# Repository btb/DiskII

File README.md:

# DiskII
 An Apple Disk II controller clone using standard EPROMs

Revision 0 of this board is broken, [here's how to fix it](https://github.com/btb/DiskII/wiki/Revision-0-errata).

[Revision 1](https://github.com/btb/DiskII/releases/tag/rev1) has all known problems fixed.

[Interactive BOM](https://btb.github.io/DiskII/bom/DiskII_rev1.html)

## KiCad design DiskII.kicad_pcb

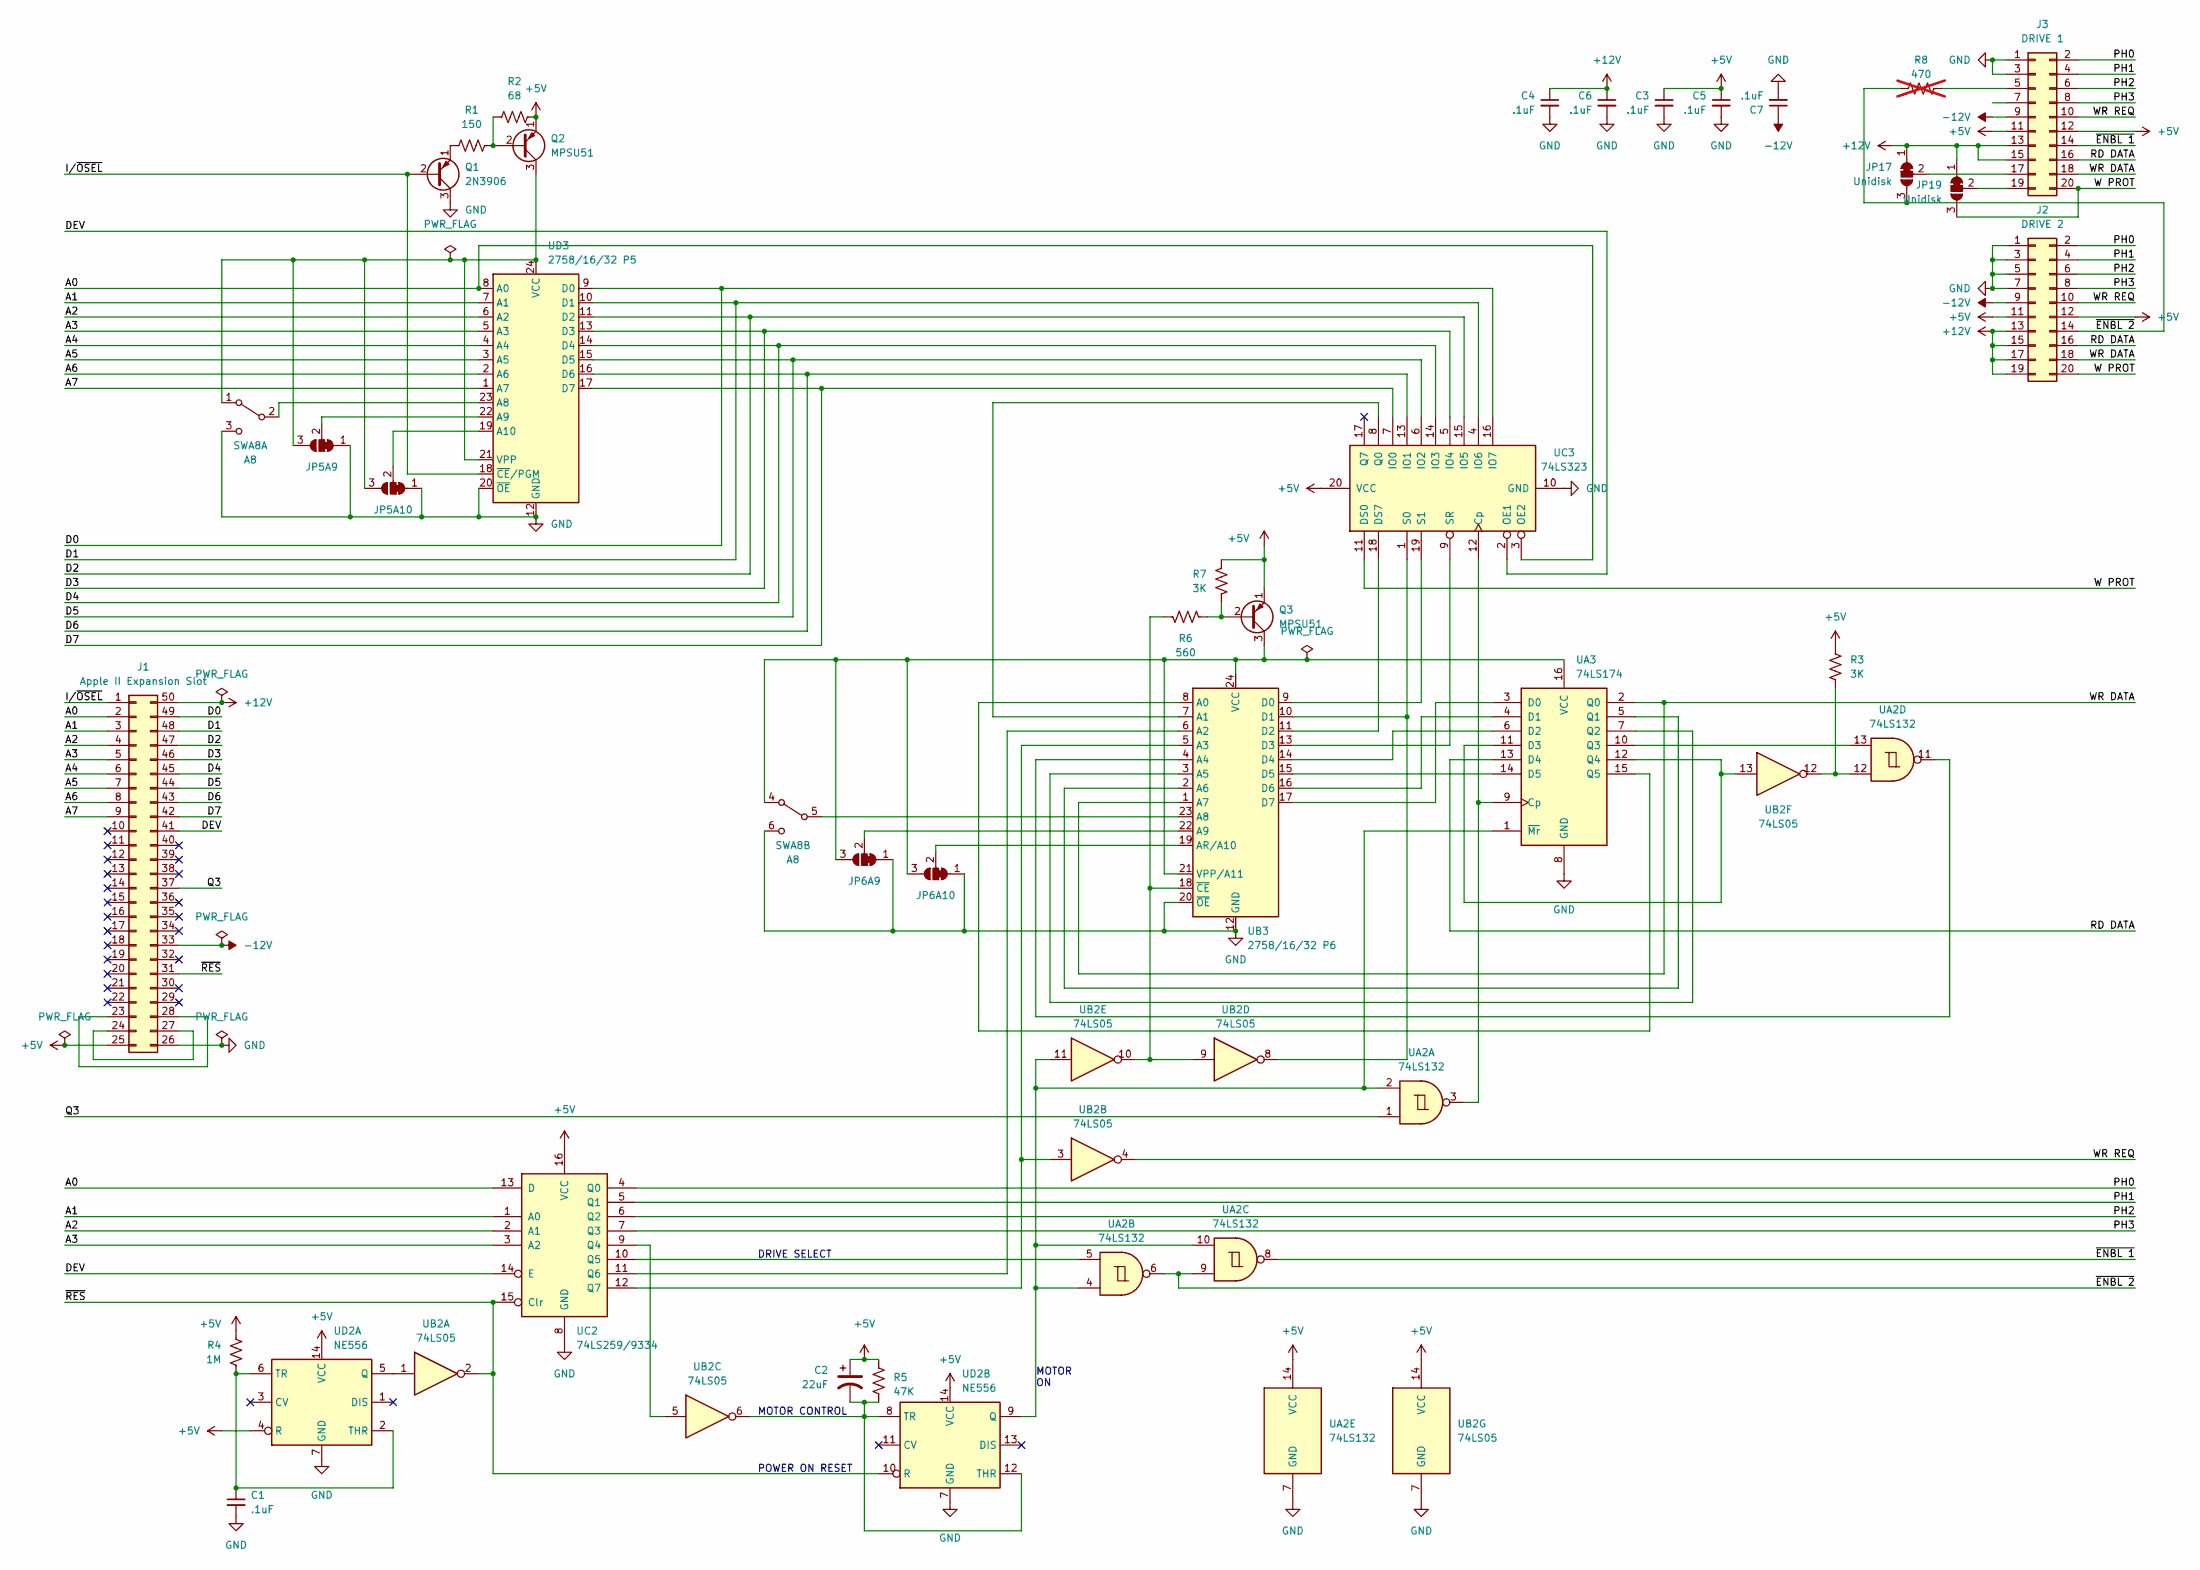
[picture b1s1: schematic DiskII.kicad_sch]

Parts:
C1, C3, C4, C5, C6, C7: .1uF; C_Rect_L7.0mm_W2.0mm_P5.00mm
C2: 22uF; CP_Radial_D8.0mm_P5.00mm
J1: Apple II Expansion Slot; Apple II Expansion Edge Connector
J2: DRIVE 2; PinHeader_2x10_P2.54mm_Horizontal
J3: DRIVE 1; PinHeader_2x10_P2.54mm_Horizontal
JP5A9, JP6A9: A9; SolderJumper-3_P1.3mm_Bridged12_RoundedPad1.0x1.5mm_NumberL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
JP5A10, JP6A10: A10; SolderJumper-3_P1.3mm_Bridged12_RoundedPad1.0x1.5mm_NumberL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
JP17, JP19: Unidisk; SolderJumper-3_P1.3mm_Bridged12_RoundedPad1.0x1.5mm
Q1: 2N3906; TO-92_Inline_Wide
Q2, Q3: MPSU51; TO-220-3_Vertical
R1: 150; R_Axial_DIN0207_L6.3mm_D2.5mm_P10.16mm_Horizontal
R2: 68; R_Axial_DIN0207_L6.3mm_D2.5mm_P10.16mm_Horizontal
R3, R7: 3K; R_Axial_DIN0207_L6.3mm_D2.5mm_P10.16mm_Horizontal
R4: 1M; R_Axial_DIN0207_L6.3mm_D2.5mm_P10.16mm_Horizontal
R5: 47K; R_Axial_DIN0207_L6.3mm_D2.5mm_P10.16mm_Horizontal
R6: 560; R_Axial_DIN0207_L6.3mm_D2.5mm_P10.16mm_Horizontal
R8: 470; R_Axial_DIN0207_L6.3mm_D2.5mm_P10.16mm_Horizontal; not fitted
SWA8: A8; PinHeader_2x03_P2.54mm_Vertical
UA2: 74LS132; DIP-14_W7.62mm
UA3: 74LS174; DIP-16_W7.62mm
UB2: 74LS05; DIP-14_W7.62mm
UB3: 2758/16/32 P6; DIP-24_W15.24mm
UC2: 74LS259/9334; DIP-16_W7.62mm
UC3: 74LS323; DIP-20_W7.62mm
UD2: NE556; DIP-14_W7.62mm
UD3: 2758/16/32 P5; DIP-24_W15.24mm

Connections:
+5V: C2.1, C3.1, C5.1, J1.25, J2.11, J2.12, J3.11, J3.12, Q2.1 (E), Q3.1 (E), R2.1, R3.1, R4.1, R5.2, R7.1, UA2.14 (VCC), UB2.14 (VCC), UC2.16 (VCC), UC3.20 (VCC), UD2.4 (R), UD2.14 (VCC)
+12V: C4.1, C6.1, J1.50, J2.13, J2.15, J2.17, J2.19, J3.13, J3.15, JP17.1 (A), JP19.1 (A)
-12V: C7.1, J1.33, J2.9, J3.9
/A0: J1.2, UC2.13 (D), UC3.3 (OE2), UD3.8 (A0)
/A1: J1.3, UC2.1 (A0), UD3.7 (A1)
/A2: J1.4, UC2.2 (A1), UD3.6 (A2)
/A3: J1.5, UC2.3 (A2), UD3.5 (A3)
/A4: J1.6, UD3.4 (A4)
/A5: J1.7, UD3.3 (A5)
/A6: J1.8, UD3.2 (A6)
/A7: J1.9, UD3.1 (A7)
/D0: J1.49, UC3.16 (IO7), UD3.9 (D0)
/D1: J1.48, UC3.4 (IO6), UD3.10 (D1)
/D2: J1.47, UC3.15 (IO5), UD3.11 (D2)
/D3: J1.46, UC3.5 (IO4), UD3.13 (D3)
/D4: J1.45, UC3.14 (IO3), UD3.14 (D4)
/D5: J1.44, UC3.6 (IO2), UD3.15 (D5)
/D6: J1.43, UC3.13 (IO1), UD3.16 (D6)
/D7: J1.42, UC3.7 (IO0), UD3.17 (D7)
/DEV: J1.41, UC2.14 (E), UC3.2 (OE1)
/I/~OSEL: J1.1, Q1.2 (B), UD3.18 (~CE/PGM)
/PH0: J2.2, J3.2, UC2.4 (Q0)
/PH1: J2.4, J3.4, UC2.5 (Q1)
/PH2: J2.6, J3.6, UC2.6 (Q2)
/PH3: J2.8, J3.8, UC2.7 (Q3)
/Q3: J1.37, UA2.1
/RD DATA: J2.16, J3.16, UA3.13 (D4)
/W PROT: J2.20, J3.20, JP19.3 (B), UC3.11 (DS0)
/WR DATA: J2.18, J3.18, UA3.2 (Q0), UB3.1 (A7)
/WR REQ: J2.10, J3.10, UB2.4
/~ENBL 1: J3.14, UA2.8
/~ENBL 2: J2.14, JP17.3 (B), R8.1, UA2.6, UA2.9
/~RES: J1.31, UB2.2, UC2.15 (Clr), UD2.10 (R)
GND: C1.2, C3.2, C4.2, C5.2, C6.2, C7.2, J1.26, J2.1, J2.3, J2.5, J2.7, J3.1, J3.3, J3.5, J3.7, JP5A9.1 (A), JP5A10.1 (A), JP6A9.1 (A), JP6A10.1 (A), Q1.3 (C), R8.2, SWA8.3 (C), SWA8.6 (C), UA2.7 (GND), UA3.8 (GND), UB2.7 (GND), UB3.12 (GND), UB3.20 (~OE), UC2.8 (GND), UC3.10 (GND), UD2.7 (GND), UD3.12 (GND), UD3.20 (~OE)
unnamed: JP5A9.3 (B), JP5A10.3 (B), Q2.3 (C), SWA8.1 (A), UD3.21 (VPP), UD3.24 (VCC)
unnamed: JP6A9.3 (B), JP6A10.3 (B), Q3.3 (C), SWA8.4 (A), UA3.16 (VCC), UB3.21 (VPP/A11), UB3.24 (VCC)
unnamed: J1.23, J1.28
unnamed: J1.24, J1.27
unnamed: J3.17, JP17.2 (C)
unnamed: J3.19, JP19.2 (C)
unnamed: JP5A9.2 (C), UD3.22 (A9)
unnamed: JP5A10.2 (C), UD3.19 (A10)
unnamed: JP6A9.2 (C), UB3.22 (A9)
unnamed: JP6A10.2 (C), UB3.19 (AR/A10)
unnamed: Q1.1 (E), R1.1
unnamed: Q2.2 (B), R1.2, R2.2
unnamed: Q3.2 (B), R6.1, R7.2
unnamed: R3.2, UA2.12, UB2.12
unnamed: SWA8.2 (B), UD3.23 (A8)
unnamed: SWA8.5 (B), UB3.23 (A8)
unnamed: UA2.3, UA3.9 (Cp), UC3.12 (Cp)
unnamed: UA3.3 (D0), UB3.17 (D7)
unnamed: UA3.4 (D1), UB3.16 (D6)
unnamed: UA3.6 (D2), UB3.14 (D4)
unnamed: UA3.11 (D3), UA3.12 (Q4), UB2.13
unnamed: UA3.14 (D5), UB3.15 (D5)
unnamed: UA3.5 (Q1), UB3.2 (A6)
unnamed: UA3.7 (Q2), UB3.3 (A5)
unnamed: UA2.13, UA3.10 (Q3)
unnamed: UA3.15 (Q5), UB3.8 (A0)
unnamed: UA2.2, UA2.4, UA2.10, UA3.1 (~Mr), UB2.11, UD2.9 (Q)
unnamed: UB3.7 (A1), UC3.8 (Q0)
unnamed: UB3.6 (A2), UC2.11 (Q6)
unnamed: UB2.3, UB3.5 (A3), UC2.12 (Q7)
unnamed: UA2.11, UB3.4 (A4)
unnamed: UB3.9 (D0), UC3.19 (S1)
unnamed: UB2.8, UB3.10 (D1), UC3.1 (S0)
unnamed: UB3.11 (D2), UC3.18 (DS7)
unnamed: UB3.13 (D3), UC3.9 (SR)
unnamed: R6.2, UB2.9, UB2.10, UB3.18 (~CE)
unnamed: UB2.5, UC2.9 (Q4)
unnamed: UA2.5, UC2.10 (Q5)
unnamed: UB2.1, UD2.5 (Q)
unnamed: C1.1, R4.2, UD2.2 (THR), UD2.6 (TR)
unnamed: C2.2, R5.1, UB2.6, UD2.8 (TR), UD2.12 (THR)

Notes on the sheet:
MOTOR ON
POWER ON RESET
DRIVE SELECT
MOTOR CONTROL

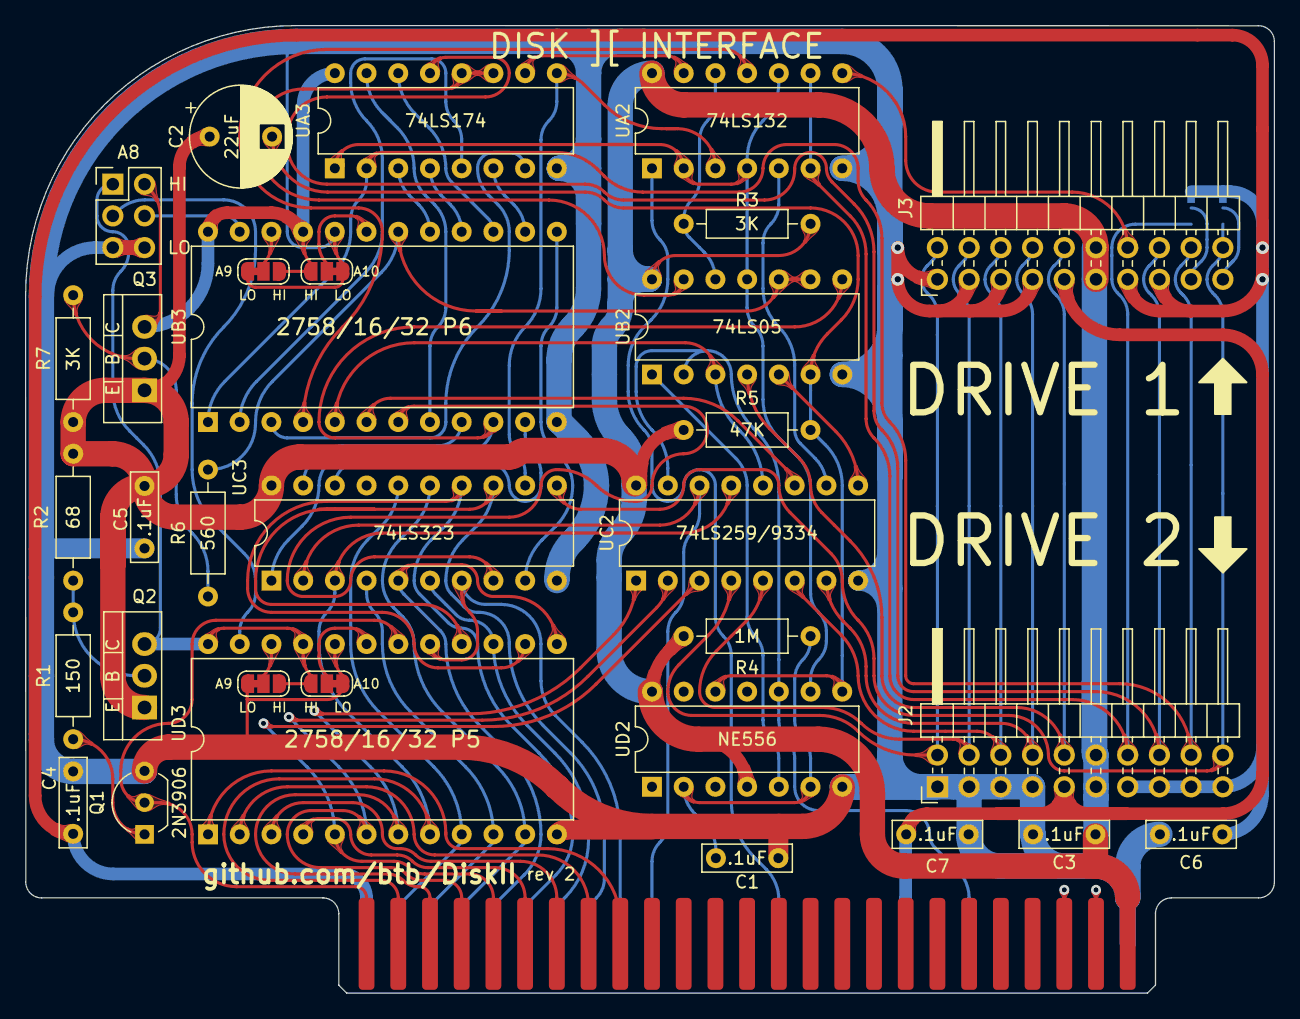
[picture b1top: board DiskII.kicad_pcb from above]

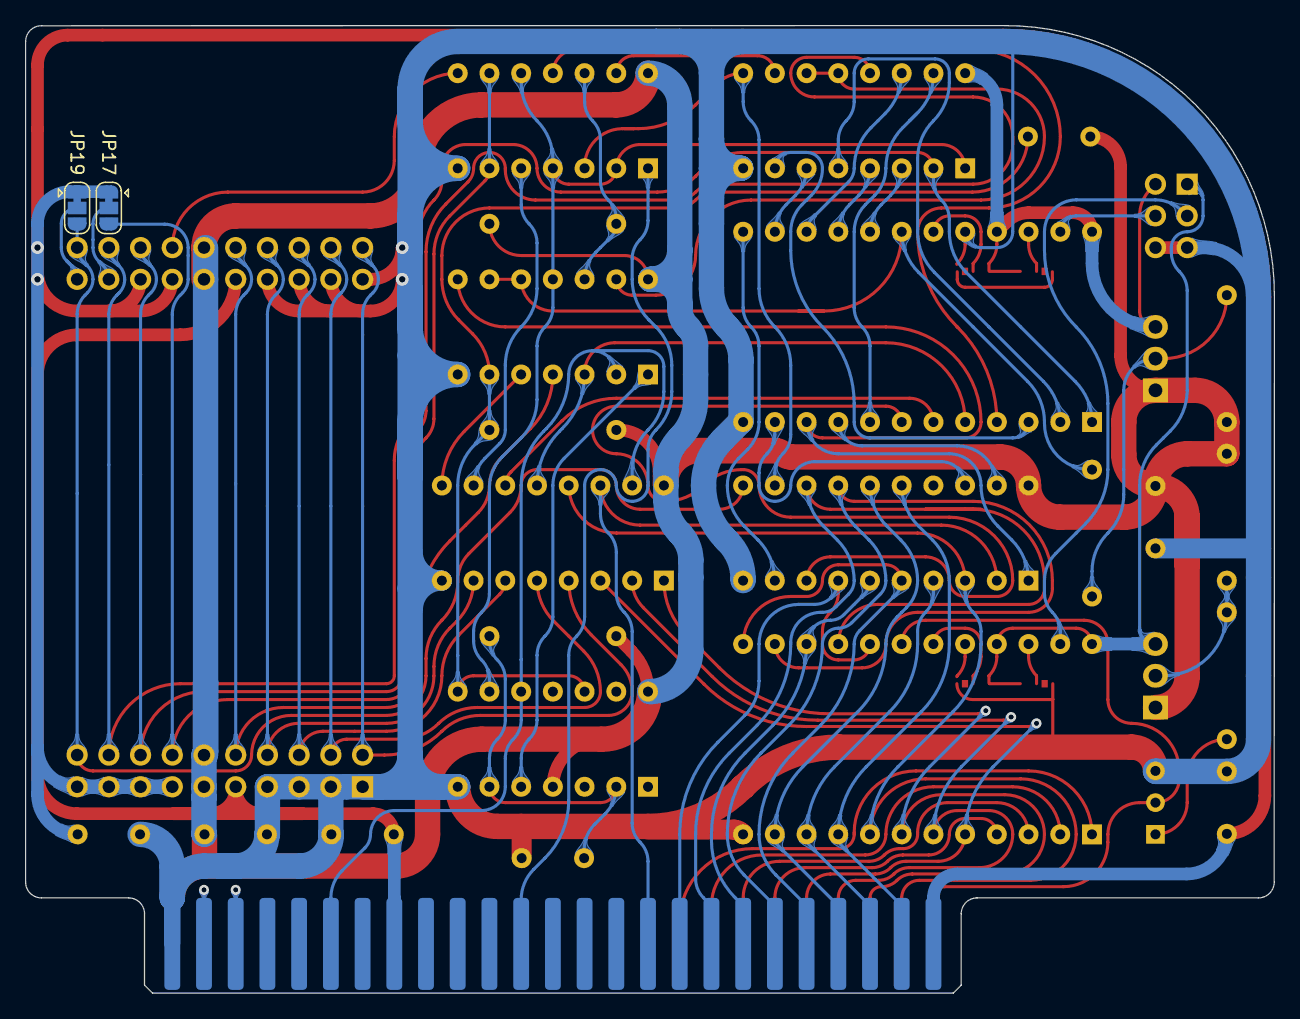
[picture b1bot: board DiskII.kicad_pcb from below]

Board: 2 copper layers, 100.0 x 77.5 mm, 35 parts (2 on the bottom side), 75 nets.

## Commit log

2022-08-03 add KiCad files
2022-08-03 add schematic pdf and gerber files
2022-08-06 add BOM
2022-08-06 Add Interactive BOM
2022-08-07 move text away from via
2022-08-07 update BOM
2022-10-20 fix misrouted data lines to shift register
    a few other minor fixes
2022-10-26 Add KiBot workflow
2022-10-26 massive fixups
2022-11-07 revision 1
2022-11-07 revision 1 gerbers
2022-11-07 update README for revision 1
2022-11-07 no zip files
2022-11-07 no gerbers
2022-11-07 ignore
2022-11-08 BOM: no solder jumpers, hide fab layer by default
2023-08-01 rev1 schematic pdf
2023-08-01 jumper to put WPROT on pin 19
2023-08-02 starting rev 2
